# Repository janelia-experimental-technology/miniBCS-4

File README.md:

# miniBSC-4
 Configurable I/O PCB for Teensy 4.1 and Max11300
 
 https://doi.org/10.25378/janelia.29669162

 System Overview

The miniBCS is a compact, general-purpose Behavioral Control System (BCS). It provides a powerful platform to control real-time experiments. It is highly adaptable in terms of types of outputs and connectors. It is also designed to be easy to use, self-documenting, inexpensive, and easy to customize.

Hardware Development

The miniBCS is designed around the Teensy processor system. Currently, the Teensy 3.5 processor board is being used. This board utilizes a 32-bit ARM processor with 120Mhz operation, 512K Flash, and 192K RAM. The Arduino programming environment makes writing and downloading code easy. A MAX11300 integrated circuit provides 12-bit bipolar ADC/DAC and other configurable IO not available on the Teensy. The various input/outputs (IOs) are brought out to various connector options, including DB9, BNC, latch connectors, and RJ9. Connectors can face vertically or horizontally. A waveform generator is also built in. builders can add a small monochrome graphic LCD and three pushbuttons to provide a simple user interface. The system is designed so that only the required features and connectors need to be added to the base board, minimizing cost and assembly time. The enclosure can be made from laser-cut material, making it easy to configure the unit, house the electronics, make attachment points, and engrave connector labels.

Capabilities (some are mutually exclusive):

    Up to three RS232 serial ports
    Host USB serial port (also used for programming)
    CAN bus
    Ethernet
    Up to 10 12-bit DACs with +/-5V, 0-10V, or -10 to 10V ranges (MAX11300)
    Up to 10 12-bit ADCs with 0-2.5, +/-5V, 0-10V, or -10 to 0V ranges (MAX11300)
    Up to 10 IOs with programmable thresholds or output ranges (MAX11300)
    8 isolated solenoid drivers with 11-35 Volt power supply range
    Frequency Generator with a range of 1Hz to 10MHz, sine, triangle, square wave
    2 temperature sensors (MAX11300)
    SPI/I2C Expansion Bus
    Up to 8 IOs that connect directly to the processor that can be programmed for:
        Interrupts
        0-3.3V DAC
        0-3.3V ADC
        3.3V digital output
        5V tolerant digital input
        PWM or servo drive
        Various timer/counter needs

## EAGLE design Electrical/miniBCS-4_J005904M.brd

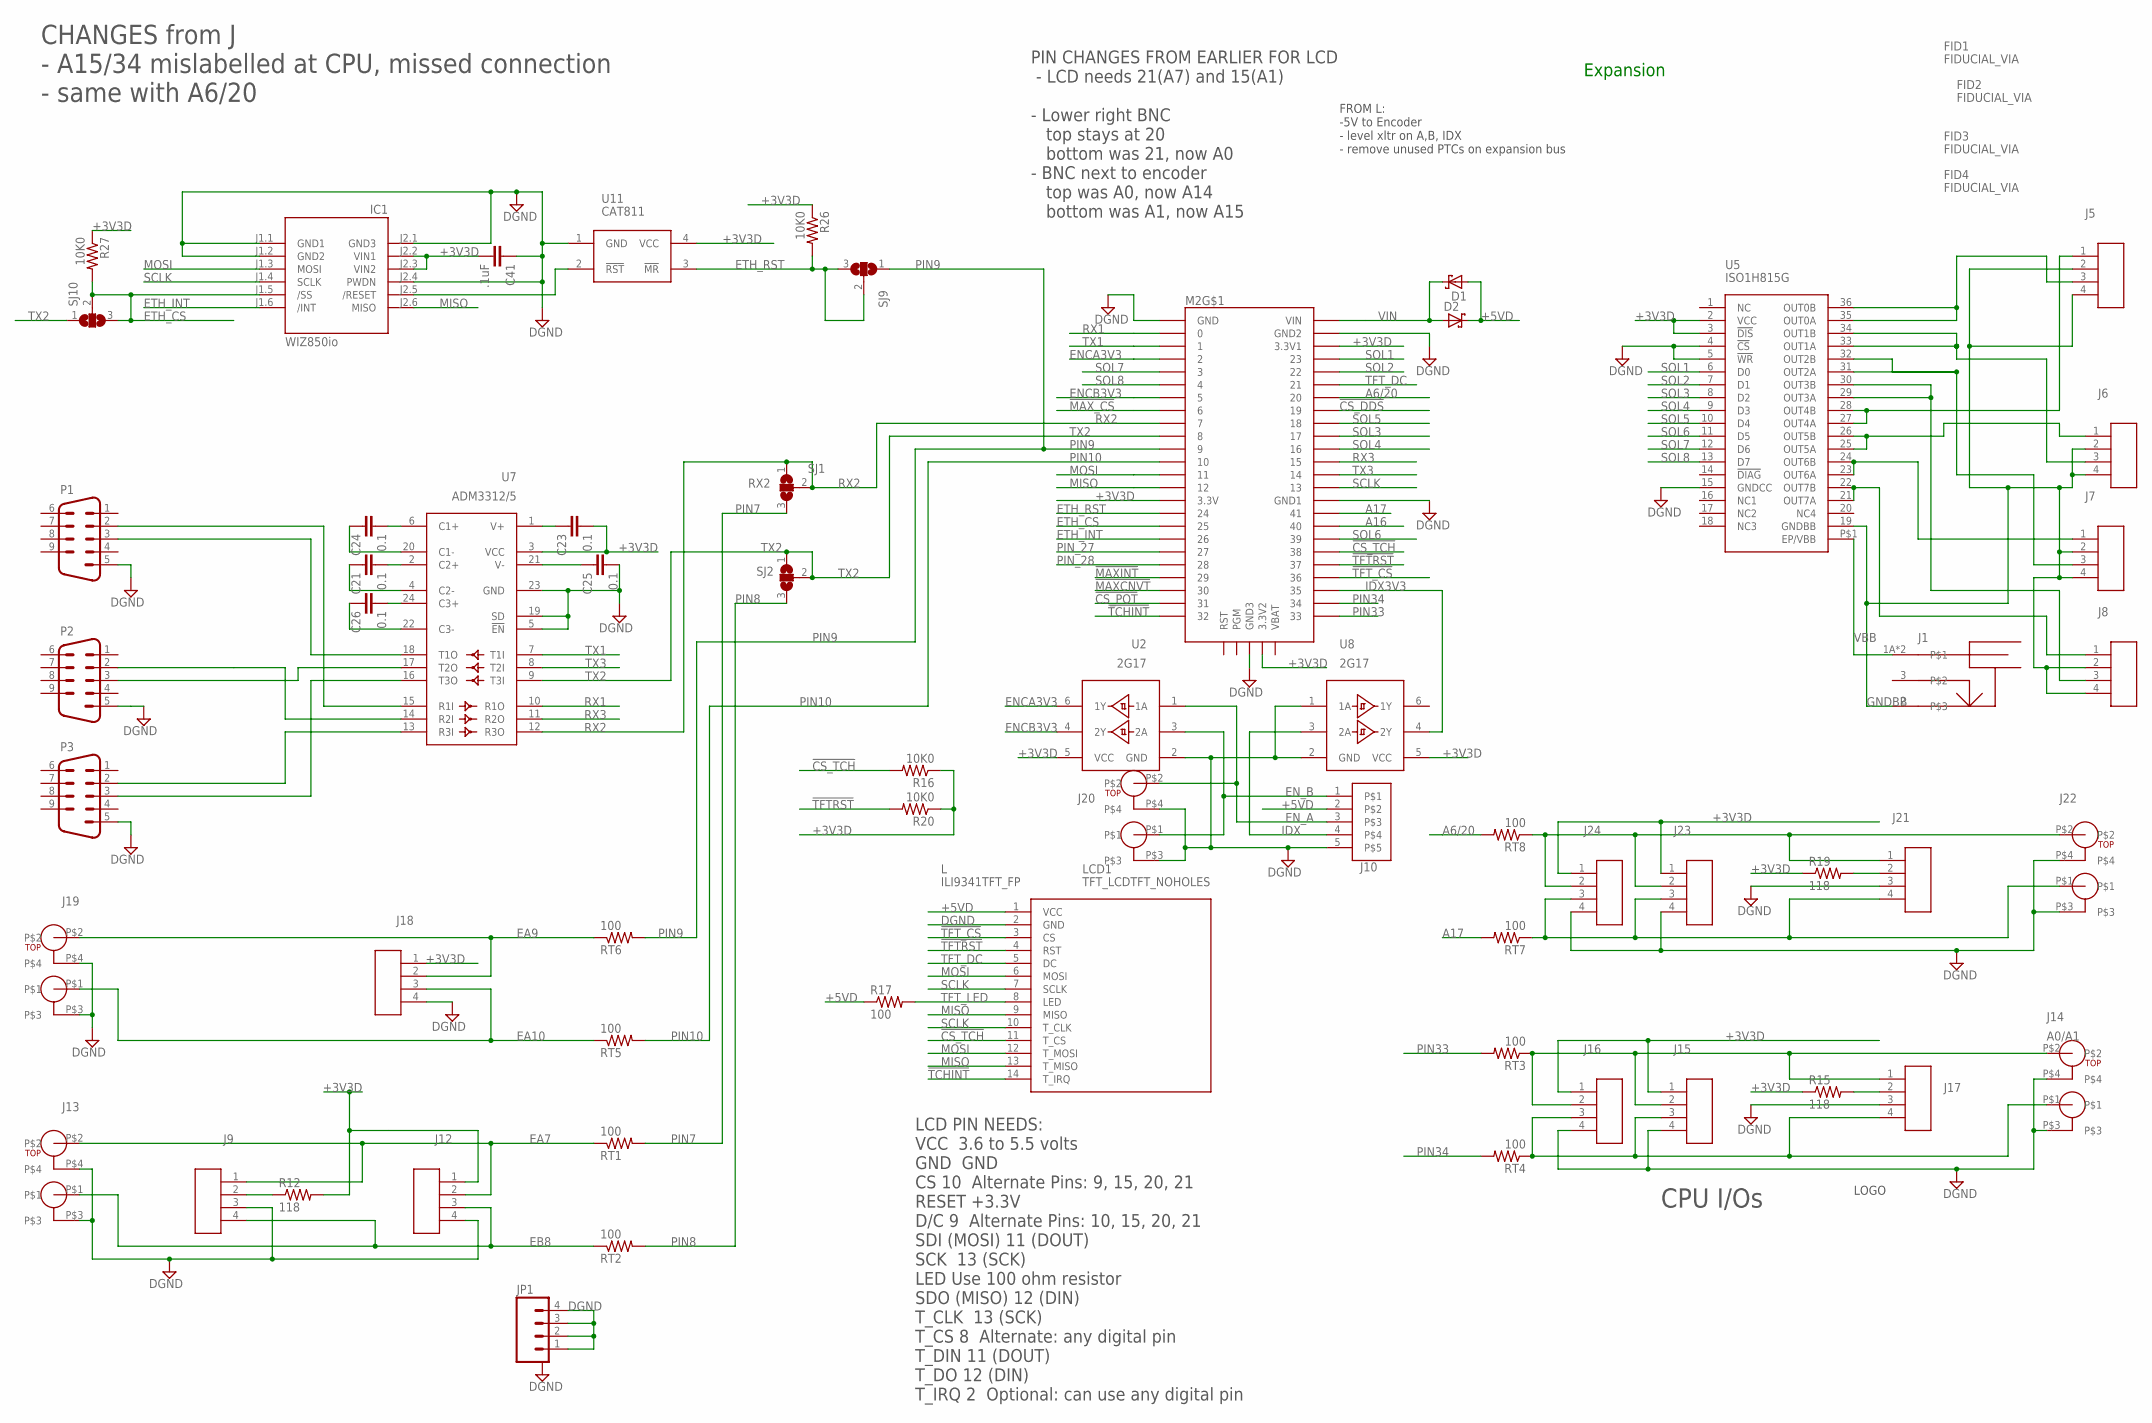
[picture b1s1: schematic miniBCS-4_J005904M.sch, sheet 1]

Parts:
C21, C23, C24, C25, C26: 0.1; 0603S
C41: .1uF; 0603S
D1, D2: SCHOTTKY-DIODESMD; SMB
FID1, FID2, FID3, FID4: FIDUCIAL_VIA
IC1: WIZ850io; WIZ820IO
J1: POWER_JACK_SHUNTPJ-002; PJ-002
J5, J6, J7, J8: CON41894804; 1894804
J9, J17, J21: RJ90432024101; 0432024101
J10: CON5AMPMODU-5; AMPMODU-5
J12, J15, J18, J23: CON4AMPMODUL-4-RA; AMPMODU-4-RA
J13, J19, J20, J22: BNC-DUAL; DUAL-BNC
J14: A0/A1; DUAL-BNC
J16, J24: CON41881464; PHOENIX_1881464
JP1: M04LOCK; 1X04_LOCK
L: ILI9341TFT_FP; ILI9341TFT_HOLES
LCD1: TFT_LCDTFT_NOHOLES; TFT_LCD_NOHOLES
M2: TEENSY4.1
P1, P2, P3: M09-182; 182-009-MALE
R12, R15, R19: 118; 0805S
R16, R20, R26, R27: 10K0; 0805S
R17: 100; 0805S
RT1, RT2, RT3, RT4, RT5, RT6, RT7, RT8: 100; 0805S
SJ1, SJ2, SJ9, SJ10: SJ2W; SJ_2
U2, U8: 2G17; SOT23-6
U5: ISO1H815G; PG-DSO-36
U7: ADM3312/5; TSSOP-24
U11: CAT811; SOT-143
U$1: JFRC-LOGOLOGO_2014_DOC; LOGO_JANELIA_2014_DOC

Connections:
!CS_DDS: M2.19/A5/SCL (19); also elsewhere on the board
!CS_POT: M2.31/A12 (31); also elsewhere on the board
!CS_TCH: LCD1.11 (T_CS), M2.38, R16.2
!MAXCNVT: M2.30; also elsewhere on the board
!MAXINT: M2.29; also elsewhere on the board
!MAX_CS: M2.6; also elsewhere on the board
!TCHINT: LCD1.14 (T_IRQ), M2.32
!TFTRST: LCD1.4 (RST), M2.37, R20.2
!TFT_CS: LCD1.3 (CS), M2.36
+3V3D: C23.2, C41.2, IC1.J2.2 (VIN1), IC1.J2.3 (VIN2), J12.1, J15.1, J16.1, J18.1, J23.1, J24.1, M2.3V3 (3.3V), M2.3V3_LO (3.3V1), M2.V33 (3.3V2), R12.2, R15.1, R16.1, R19.1, R20.1, R26.1, R27.1, U2.5 (VCC), U5.2 (VCC), U5.3 (!DIS), U7.3 (VCC), U8.5 (VCC), U11.4 (VCC); also elsewhere on the board
+5VD: D1.A, D2.C, J10.2, LCD1.1 (VCC), R17.1; also elsewhere on the board
A6/20: M2.20/A6 (20), RT8.2
A16: M2.40; also elsewhere on the board
A17: M2.41, RT7.2
DGND: C25.2, C41.1, IC1.J1.1 (GND1), IC1.J1.2 (GND2), IC1.J2.1 (GND3), IC1.J2.4 (PWDN), J9.3, J10.5, J12.4, J13.P$3, J13.P$4, J14.P$3, J14.P$4, J15.4, J16.4, J17.3, J18.4, J19.P$3, J19.P$4, J20.P$3, J20.P$4, J21.3, J22.P$3, J22.P$4, J23.4, J24.4, JP1.1, JP1.2, JP1.3, JP1.4, LCD1.2 (GND), M2.AGND (GND2), M2.GND, M2.GND1, M2.GND2 (GND3), P1.5, P2.5, P3.5, U2.2 (GND), U5.4 (!CS), U5.5 (!WR), U5.15 (GNDCC), U7.5 (!EN), U7.19 (SD), U7.23 (GND), U8.1 (1A), U8.2 (GND), U11.1 (GND); also elsewhere on the board
EA5: J14.P$2, J15.2, J16.2, J17.1, RT3.1
EA6: J21.1, J22.P$2, J23.2, J24.2, RT8.1
EA7: J9.1, J12.2, J13.P$2, RT1.1
EA9: J18.2, J19.P$2, RT6.1
EA10: J18.3, J19.P$1, RT5.1
EB5: J14.P$1, J15.3, J16.3, J17.4, RT4.1
EB6: J21.4, J22.P$1, J23.3, J24.3, RT7.1
EB8: J9.4, J12.3, J13.P$1, RT2.1
ENCA3V3: M2.2, U2.6 (1Y)
ENCB3V3: M2.5, U2.4 (2Y)
EN_A: J10.3, J20.P$2, U2.1 (1A)
EN_B: J10.1, J20.P$1, U2.3 (2A)
ETH_CS: IC1.J1.5 (/SS), M2.25, R27.2, SJ10.2, SJ10.3
ETH_INT: IC1.J1.6 (/INT), M2.26
ETH_RST: M2.24, R26.2, SJ9.2, SJ9.3, U11.3 (!MR)
GNDBB: J1.2, J5.2, J5.4, J6.2, J6.4, J7.2, J7.4, J8.2, J8.4, U5.19 (GNDBB)
IDX: J10.4, U8.3 (2A)
IDX3V3: M2.35, U8.4 (2Y)
MISO: IC1.J2.6 (MISO), LCD1.9 (MISO), LCD1.13 (T_MISO), M2.12/MISO (12); also elsewhere on the board
MOSI: IC1.J1.3 (MOSI), LCD1.6 (MOSI), LCD1.12 (T_MOSI), M2.11/MOSI (11); also elsewhere on the board
unnamed: J7.1, U5.23 (OUT6A), U5.24 (OUT6B)
unnamed: J9.2, R12.1
unnamed: J21.2, R19.2
unnamed: J17.2, R15.2
unnamed: P2.2, U7.14 (R2I)
unnamed: J5.1, U5.27 (OUT4A), U5.28 (OUT4B)
unnamed: P2.3, U7.17 (T2O)
unnamed: C23.1, U7.1 (V+)
unnamed: J6.1, U5.25 (OUT5A), U5.26 (OUT5B)
unnamed: C25.1, U7.21 (V-)
unnamed: P1.3, U7.18 (T1O)
unnamed: J8.3, U5.29 (OUT3A), U5.30 (OUT3B)
unnamed: J8.1, U5.21 (OUT7A), U5.22 (OUT7B)
unnamed: C26.2, U7.24 (C3+)
unnamed: C26.1, U7.22 (C3-)
unnamed: C21.1, U7.4 (C2-)
unnamed: C21.2, U7.2 (C2+)
unnamed: C24.1, U7.20 (C1-)
unnamed: P1.2, U7.15 (R1I)
unnamed: J5.3, U5.35 (OUT0A), U5.36 (OUT0B)
unnamed: C24.2, U7.6 (C1+)
unnamed: J6.3, U5.33 (OUT1A), U5.34 (OUT1B)
unnamed: J7.3, U5.31 (OUT2A), U5.32 (OUT2B)
unnamed: P3.3, U7.16 (T3O)
unnamed: IC1.J2.5 (/RESET), U11.2 (!RST)
PIN7: RT1.2, SJ1.3
PIN8: RT2.2, SJ2.3
PIN9: M2.9, RT6.2, SJ9.1
PIN10: M2.10/CS (10), RT5.2
PIN33: M2.33, RT3.2
PIN34: M2.34, RT4.2
PIN_27: M2.27; also elsewhere on the board
PIN_28: M2.28; also elsewhere on the board
RX1: M2.0/RX (0), U7.10 (R1O)
RX2: M2.7, SJ1.1, SJ1.2, U7.12 (R3O)
RX3: M2.15/A1 (15), U7.11 (R2O)
RX3_232: P3.2, U7.13 (R3I)
SCLK: IC1.J1.4 (SCLK), LCD1.7 (SCLK), LCD1.10 (T_CLK), M2.13/SCK (13); also elsewhere on the board
SOL1: M2.23/A9 (23), U5.6 (D0)
SOL2: M2.22/A8 (22), U5.7 (D1)
SOL3: M2.17/A3 (17), U5.8 (D2)
SOL4: M2.16/A2 (16), U5.9 (D3)
SOL5: M2.18/A4/SDA (18), U5.10 (D4)
SOL6: M2.39, U5.11 (D5)
SOL7: M2.3, U5.12 (D6)
SOL8: M2.4, U5.13 (D7)
TFT_DC: LCD1.5 (DC), M2.21/A7 (21)
TFT_LED: LCD1.8 (LED), R17.2
TX1: M2.1/TX (1), U7.7 (T1I)
TX2: M2.8, SJ2.1, SJ2.2, SJ10.1, U7.9 (T3I)
TX3: M2.14/A0 (14), U7.8 (T2I)
VBB: J1.1A, J1.1B, U5.P$1 (EP/VBB)
VIN: D1.C, D2.A, M2.VIN

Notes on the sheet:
CPU I/Os
Expansion
CHANGES from J - A15/34 mislabelled at CPU, missed connection - same with A6/20
PIN CHANGES FROM EARLIER FOR LCD - LCD needs 21(A7) and 15(A1) - Lower right BNC top stays at 20 bottom was 21, now A0 - BNC next to encoder top was A0, now A14 bottom was A1, now A15
LCD PIN NEEDS: VCC 3.6 to 5.5 volts GND GND CS 10 Alternate Pins: 9, 15, 20, 21 RESET +3.3V D/C 9 Alternate Pins: 10, 15, 20, 21 SDI (MOSI) 11 (DOUT) SCK 13 (SCK) LED Use 100 ohm resistor SDO (MISO) 12 (DIN) T_CLK 13 (SCK) T_CS 8 Alternate: any digital pin T_DIN 11 (DOUT) T_DO 12 (DIN) T_IRQ 2 Opti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
FROM L: -5V to Encoder - level xltr on A,B, IDX - remove unused PTCs on expansion bus

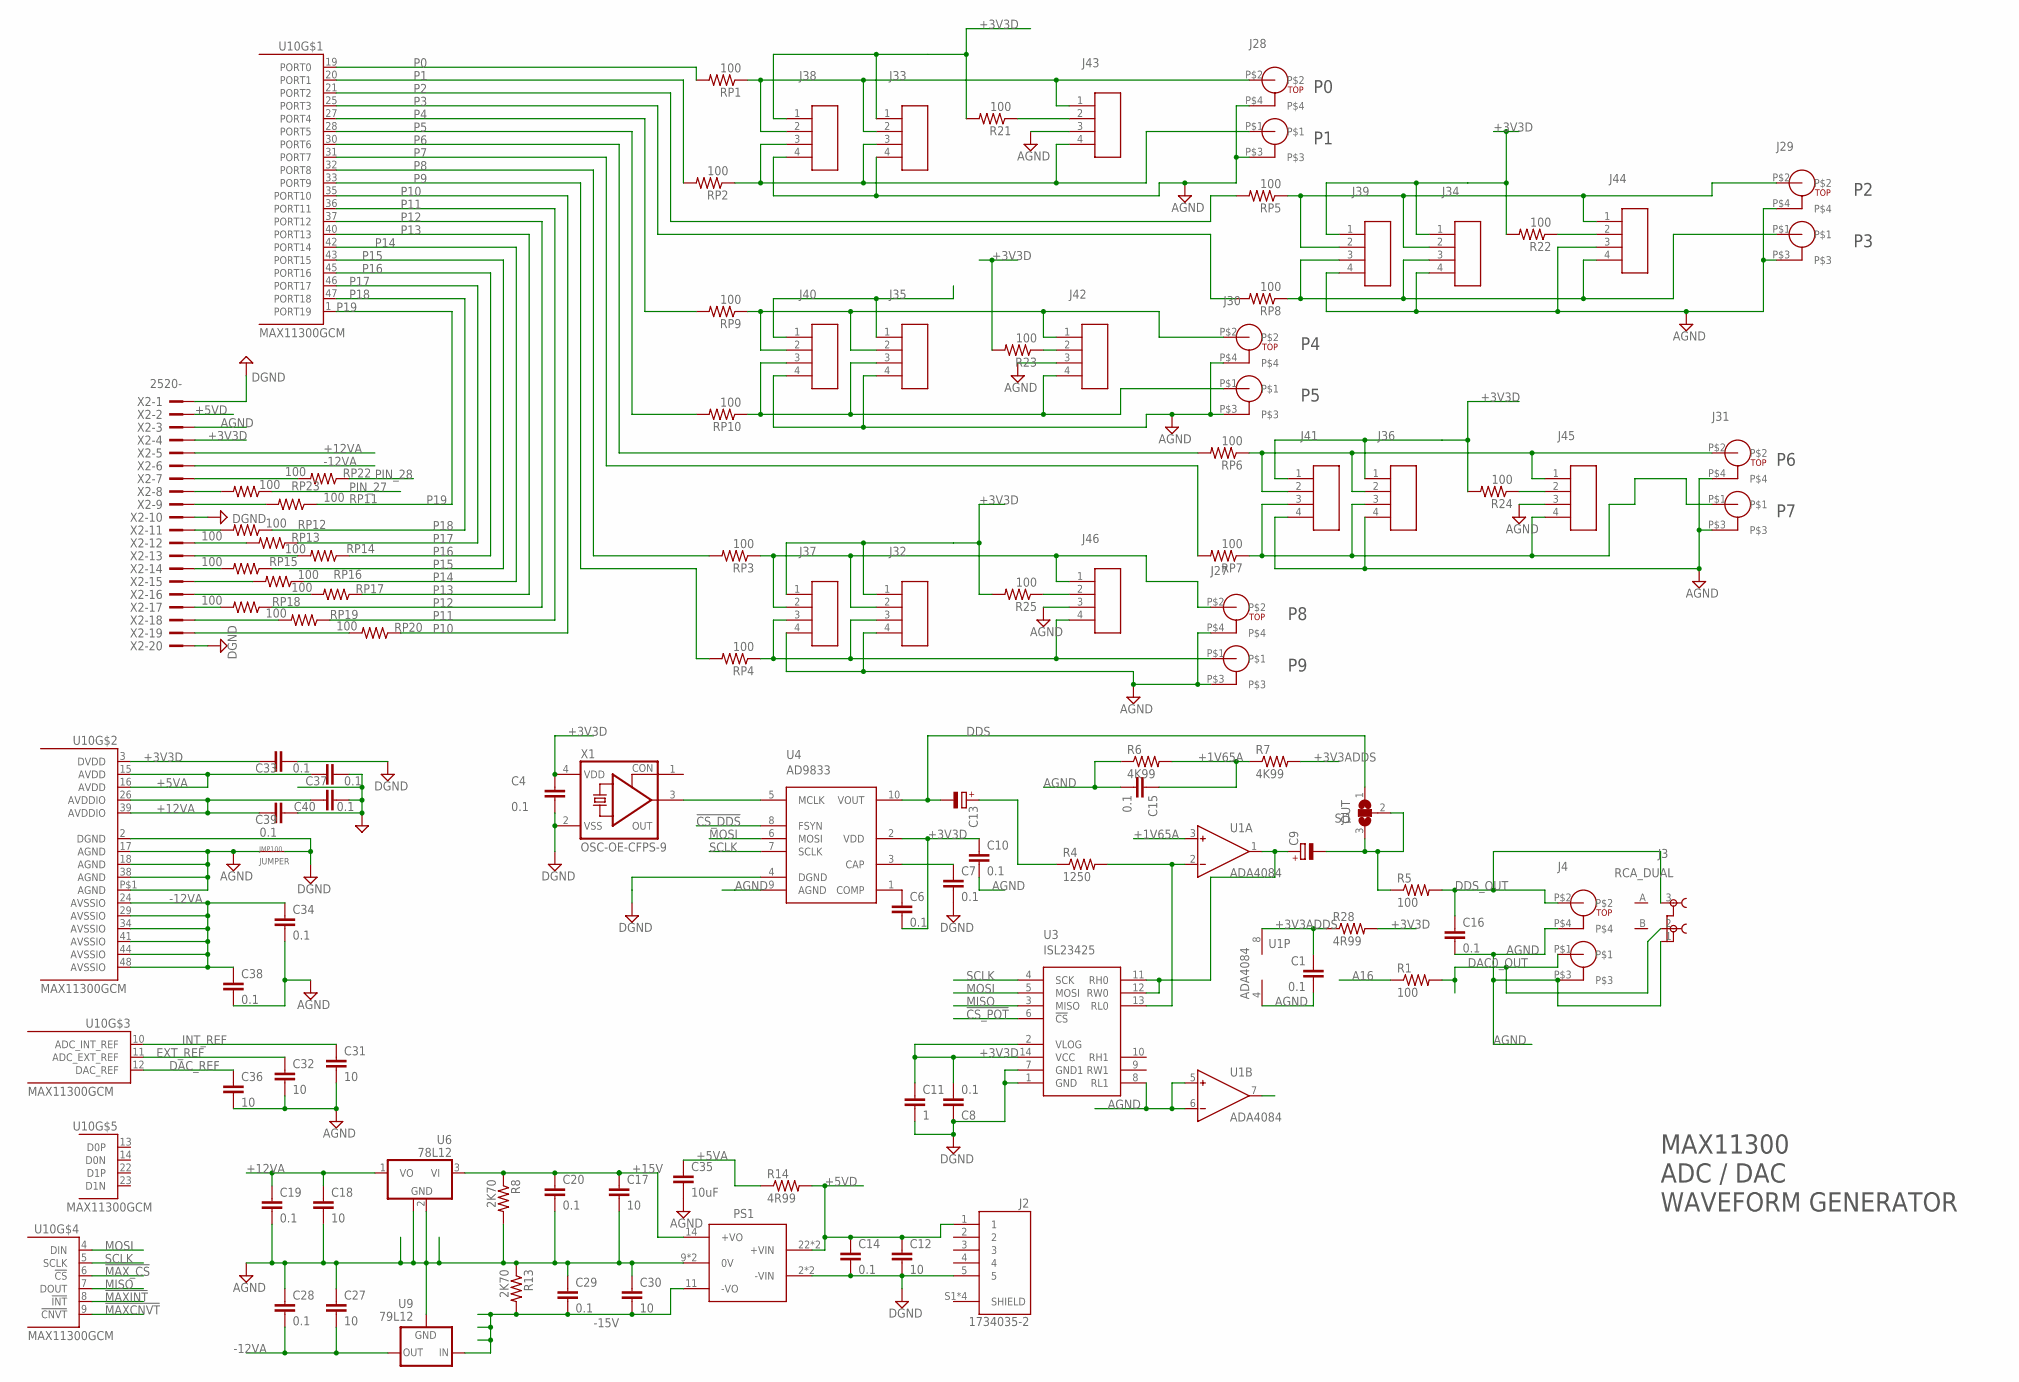
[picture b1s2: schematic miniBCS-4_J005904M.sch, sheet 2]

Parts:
C1, C4, C6, C7, C8, C10, C14, C15, C19, C20, C28, C29, C33, C34, C37, C38, C39, C40: 0.1; 0603S
C9, C13: CPOL-EUC; PANASONIC_C
C11: 1; 0805S
C12, C17, C18, C27, C30, C31, C32, C36: 10; 1206S
C16: 0.1; 0805S
C35: 10uF; 1206S
J2: 1734035-2; CONN_1734035-2
J3: RCA_DUAL; RCJ-22XX
J4, J27, J28, J29, J30, J31: BNC-DUAL; DUAL-BNC
J32, J33, J34, J35, J36: CON4AMPMODUL-4-RA; AMPMODU-4-RA
J37, J38, J39, J40, J41: CON41881464; PHOENIX_1881464
J42, J43, J44, J45, J46: RJ90432024101; 0432024101
JMP100: JUMPER
OUT: SJ1; SJ_2
PS1: DC-DC_NTANDTD; NDTD
R1, R5, R21, R22, R23, R24, R25: 100; 0805S
R4: 1250; 0805S
R6, R7: 4K99; 0805S
R8, R13: 2K70; 0805S
R14, R28: 4R99; 0805S
RP1, RP2, RP3, RP4, RP5, RP6, RP7, RP8, RP9, RP10, RP11, RP12, RP13, RP14, RP15, RP16, RP17, RP18, RP19, RP20, RP22, RP23: 100; 0805S
U1: ADA4084; SO8
U3: ISL23425; TSSOP14
U4: AD9833; MSOP10
U6: 78L12; SOT89
U9: 79L12; SOT89
U10: MAX11300GCM; TQFP48
X1: OSC-OE-CFPS-9; 5.2X3.4-4-PAD
X2: 2520-; PAK100/2500-20

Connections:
!CS_DDS: U4.8 (FSYN); also elsewhere on the board
!CS_POT: U3.6 (!CS); also elsewhere on the board
!MAXCNVT: U10.9 (!CNVT!); also elsewhere on the board
!MAXINT: U10.8 (!INT!); also elsewhere on the board
!MAX_CS: U10.6 (!CS!); also elsewhere on the board
+1V65A: C15.1, R6.2, R7.1, U1.3 (IN+)
+3V3ADDS: C1.1, R7.2, R28.1, U1.8 (V+)
+3V3D: C4.1, C6.2, C8.2, C10.1, C11.1, C33.1, J32.1, J33.1, J34.1, J36.1, J37.1, J38.1, J39.1, J41.1, R21.2, R22.2, R23.2, R24.2, R25.2, R28.2, U3.2 (VLOG), U3.14 (VCC), U4.2 (VDD), U10.3 (DVDD), X1.4 (VDD), X2.4; also elsewhere on the board
+5VA: C35.1, C37.1, R14.1, U10.15 (AVDD), U10.16 (AVDD)
+5VD: C12.1, C14.1, J2.1, PS1.22 (+VIN), PS1.23 (+VIN), R14.2, X2.2; also elsewhere on the board
+12VA: C18.1, C19.1, C39.1, C40.1, U6.1 (VO), U10.26 (AVDDIO), U10.39 (AVDDIO), X2.5
+15V: C17.1, C20.1, PS1.14 (+VO), R8.1, U6.3 (VI)
-12VA: C27.2, C28.2, C34.1, C38.1, U9.3 (OUT), U10.24 (AVSSIO), U10.29 (AVSSIO), U10.34 (AVSSIO), U10.41 (AVSSIO), U10.44 (AVSSIO), U10.48 (AVSSIO), X2.6
-15V: C29.2, C30.2, PS1.11 (-VO), R13.2, U9.2 (IN), U9.2@1 (IN)
A16: R1.1; also elsewhere on the board
AGND: C1.2, C10.2, C15.2, C16.2, C17.2, C18.2, C19.2, C20.2, C27.1, C28.1, C29.1, C30.1, C31.2, C32.2, C34.2, C35.2, C36.2, C37.2, C38.2, C39.2, C40.2, J3.1, J4.P$3, J4.P$4, J27.P$3, J27.P$4, J28.P$3, J28.P$4, J29.P$3, J29.P$4, J30.P$3, J30.P$4, J31.P$3, J31.P$4, J32.4, J33.4, J34.4, J35.4, J36.4, J37.4, J38.4, J39.4, J40.4, J41.4, J42.3, J43.3, J44.3, J45.3, J46.3, JMP100.1, PS1.9 (0V), PS1.16 (0V), R6.1, R8.2, R13.1, U1.4 (V-), U1.5 (IN+), U1.6 (IN-), U3.8 (RL1), U4.9 (AGND), U6.2 (GND), U6.2@1 (GND), U9.1 (GND), U10.17 (AGND), U10.18 (AGND), U10.38 (AGND), U10.P$1 (AGND), X2.3
DAC0_OUT: J3.2, J4.P$1, R1.2
DAC_REF: C36.1, U10.12 (DAC_REF)
DDS: C13.-, OUT.1, U4.10 (VOUT)
DDS_OUT: C16.1, J3.3, J4.P$2, R5.2
DGND: C4.2, C7.2, C8.1, C11.2, C12.2, C14.2, C33.2, J2.5, JMP100.2, PS1.2 (-VIN), PS1.3 (-VIN), U3.1 (GND), U3.7 (GND1), U4.4 (DGND), U10.2 (DGND), X1.2 (VSS), X2.1, X2.10, X2.20; also elsewhere on the board
EA: J28.P$2, J33.2, J38.2, J43.1, RP1.1
EA1: J29.P$2, J34.2, J39.2, J44.1, RP5.1
EA2: J30.P$2, J35.2, J40.2, J42.1, RP9.1
EA3: J31.P$2, J36.2, J41.2, J45.1, RP6.1
EA4: J27.P$2, J32.2, J37.2, J46.1, RP3.1
EB: J28.P$1, J33.3, J38.3, J43.4, RP2.1
EB1: J29.P$1, J34.3, J39.3, J44.4, RP8.1
EB2: J30.P$1, J35.3, J40.3, J42.4, RP10.1
EB3: J31.P$1, J36.3, J41.3, J45.4, RP7.1
EB4: J27.P$1, J32.3, J37.3, J46.4, RP4.1
EXT_REF: C32.1, U10.11 (ADC_EXT_REF)
INT_REF: C31.1, U10.10 (ADC_INT_REF)
MISO: U3.3 (MISO), U10.7 (DOUT); also elsewhere on the board
MOSI: U3.5 (MOSI), U4.6 (MOSI), U10.4 (DIN); also elsewhere on the board
unnamed: RP23.2, X2.8
unnamed: U4.5 (MCLK), X1.3 (OUT)
unnamed: C7.1, U4.3 (CAP)
unnamed: C6.1, U4.1 (COMP)
unnamed: J43.2, R21.1
unnamed: J42.2, R23.1
unnamed: J46.2, R25.1
unnamed: C13.+, R4.1
unnamed: J45.2, R24.1
unnamed: R4.2, U1.2 (IN-), U3.13 (RL0)
unnamed: C9.+, U1.1 (OUT), U3.11 (RH0), U3.12 (RW0)
unnamed: J44.2, R22.1
unnamed: RP15.2, X2.14
unnamed: RP14.2, X2.13
unnamed: RP20.2, X2.19
unnamed: RP19.2, X2.18
unnamed: RP18.2, X2.17
unnamed: RP17.2, X2.16
unnamed: RP16.2, X2.15
unnamed: RP13.2, X2.12
unnamed: RP12.2, X2.11
unnamed: RP11.2, X2.9
unnamed: RP22.2, X2.7
P0: RP1.2, U10.19 (PORT0)
P1: RP2.2, U10.20 (PORT1)
P2: RP5.2, U10.21 (PORT2)
P3: RP8.2, U10.25 (PORT3)
P4: RP9.2, U10.27 (PORT4)
P5: RP10.2, U10.28 (PORT5)
P6: RP6.2, U10.30 (PORT6)
P7: RP7.2, U10.31 (PORT7)
P8: RP3.2, U10.32 (PORT8)
P9: RP4.2, U10.33 (PORT9)
P10: RP20.1, U10.35 (PORT10)
P11: RP19.1, U10.36 (PORT11)
P12: RP18.1, U10.37 (PORT12)
P13: RP17.1, U10.40 (PORT13)
P14: RP16.1, U10.42 (PORT14)
P15: RP15.1, U10.43 (PORT15)
P16: RP14.1, U10.45 (PORT16)
P17: RP13.1, U10.46 (PORT17)
P18: RP12.1, U10.47 (PORT18)
P19: RP11.1, U10.1 (PORT19)
PIN_27: RP23.1; also elsewhere on the board
PIN_28: RP22.1; also elsewhere on the board
PWR_P4-5: J35.1, J40.1
SCLK: U3.4 (SCK), U4.7 (SCLK), U10.5 (SCLK); also elsewhere on the board
SJ1: C9.-, OUT.2, OUT.3, R5.1

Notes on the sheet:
MAX11300 ADC / DAC WAVEFORM GENERATOR

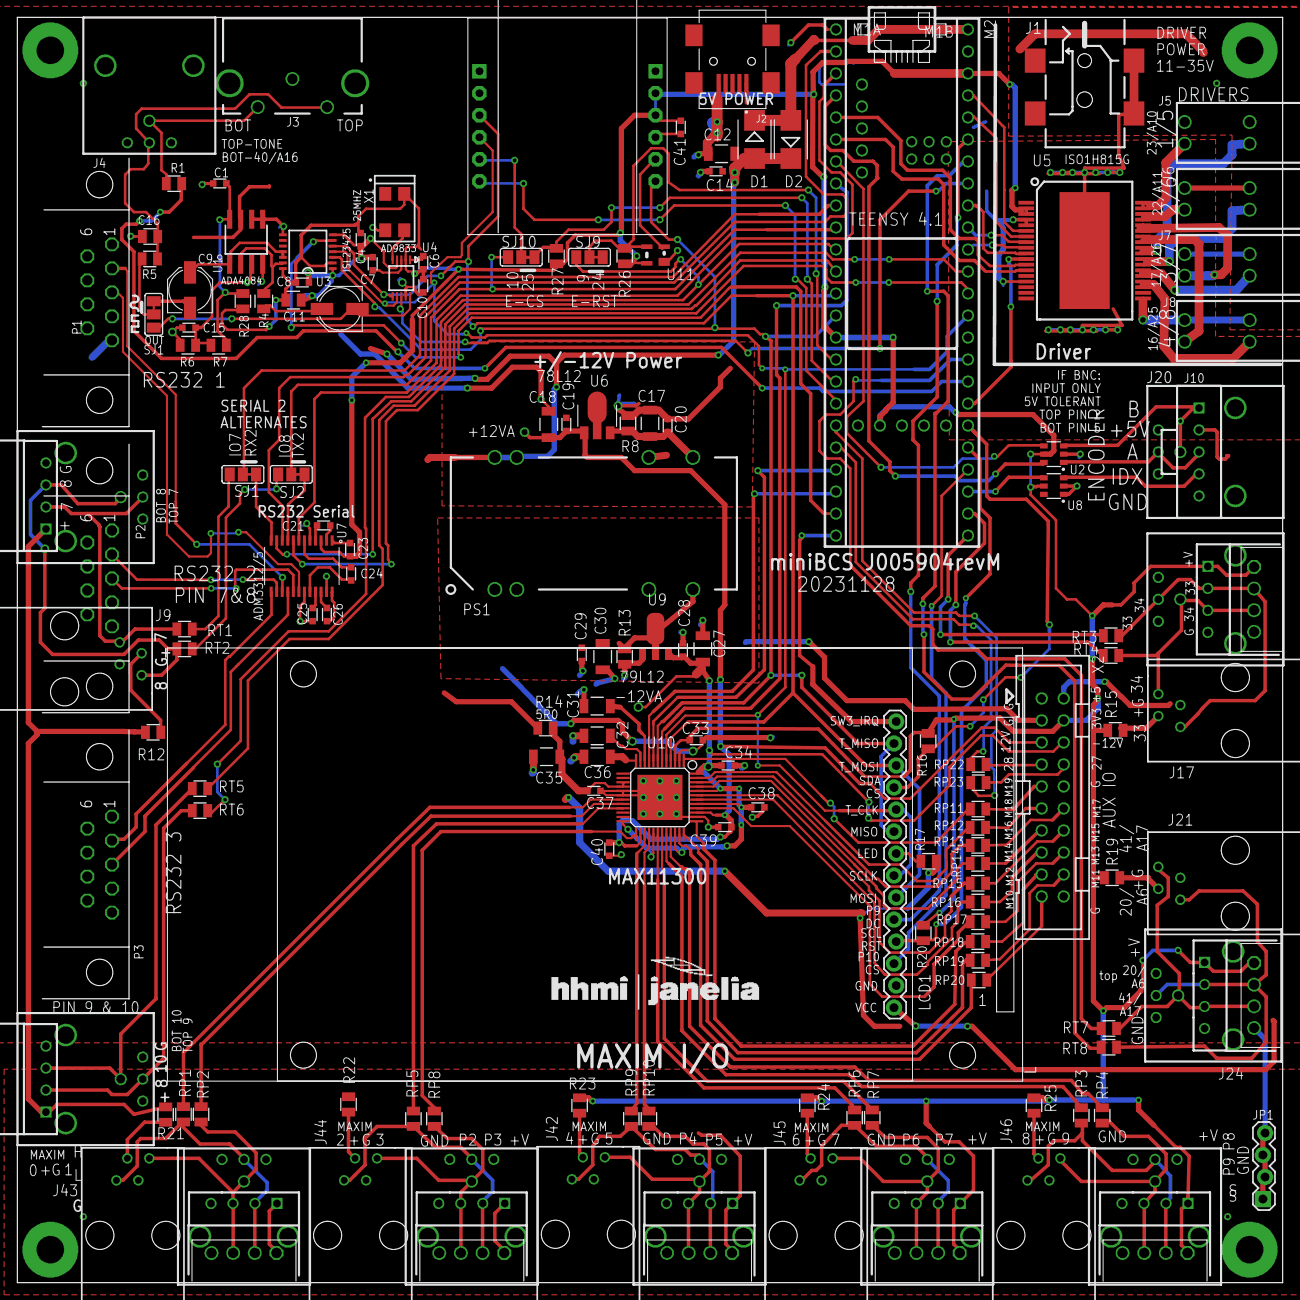
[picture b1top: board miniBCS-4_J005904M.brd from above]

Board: 2 copper layers, 146.1 x 146.1 mm, 167 parts (1 on the bottom side), 157 nets.

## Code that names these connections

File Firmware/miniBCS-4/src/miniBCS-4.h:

// ----------------------------------------------------------------------------
// miniBCS
// 
// functions needed for the miniBCS
//  set up solenoid pins, pushbutton pins 
//
// Author: Steve Sawtelle
// HHMI Janelia ID&F
// ----------------------------------------------------------------------------

// ---- VERSIONS  ----
#define  miniBCS_VERSION ((uint32_t) 20231129) 

// 0231129 sws
// - remove depracted Button code
// - changes for 'M' board with Teensy 4.1

// 20230518 sws
// - SOL7PIN was set to pin 4 and SOL8 to pin 3, but hardware is opposite, fix in FW

// 20221205 sws
// - solenoid pins 5-8 on Teesny 3.5 cannot be used as digital out
//   so set them the same as the T4.1. This will interfere with CAN 

// 20220822 sws
//  - add GPO pins 16 to 19 NOTE: Should also extend GPI and analog as well

// 20220613 sws 
// - alt pins for Teensy 4.1 - here and .cpp

// 20190322 sws
// - add CS setups for TFT and touchscreen so BCS can init properly

// 20190315 sws
// - mods for REV G boards
//  	- LCDCS now SPAREpin
//		- pin 15 now TFT CS
//		- SCL now TFT reset
//		- SDA now touchscreen CS
// 		- SW1 is TS int
// 		- 21 is TFT data/command

// 20170906 sws
// - add MAX code
// - workaround for problem with SPI settings
// 20170824 sws
// - change PB to use HW debounce
// - add encoder

// 20170817
// - started


#ifndef miniBCS_H
#define miniBCS_H

#include <SPI.h>

//volatile uint8_t _pushButtons = 0;

class miniBCS
{
 public:
 
//=======================================
// === P I N    D E F I N I T I O N S ===
// ======================================

#define RX1pin    0   // Serial 1 RX 
#define TX1pin    1   // Serial 1 TX
#define ENCApin   2   // encoder 'A' pin
#define SOL7pin   3 // Solenoid 7 pin
#define SOL8pin   4 // Solenoid 8 pin
#define ENCBpin   5   // encoder 'B' pin
#define MAXCSpin  6   // Chip Select for MAX112300
#ifdef ARDUINO_TEENSY41
#define RX2pin    7   // 
#else
#define RX3pin    7   // Serial 3 RX or 
#endif
#define PIN7      7   //   IO pin, with PWM
#ifdef ARDUINO_TEENSY41
#define TX2pin    8   // 
#else
#define TX3pin    8   // Serial 3 TX or
#endif
#define PIN8      8   //   IO pin with PWM
#define PIN9      9   //   IO pin with PWM
#ifndef ARDUINO_TEENSY41
#define RX2pin    9   // Serial 2 RX or
#define TX2pin    10  // Serial 3 TX or
#endif
#define PIN10     10  //   IO pin with PWM
#define ETHCSpin  10  // or alternate ethernet CS
#define MOSIpin   11  // SPI MOSI
#define MISOpin   12  // SPI MISO
#define SCLKpin   13  // SPI Clock
#ifdef ARDUINO_TEENSY41
#define TX3pin    14   // 
#endif
#define A0pin     14  // Analog in A0
#ifdef ARDUINO_TEENSY41
#define RX3pin    15
#else
#define TFTCSpin  15  // TFT chip select 
#endif
#define SOL4pin   16  // Solenoid 4 pin
#define SOL3pin   17  // Solenoid 3 pin
#define SOL5pin   18  // Solenoid 5 pin
#define DDSCSpin  19  // Chip Select for DDS
#define A6pin     20  // Analog in A6 
#define PIN20     20  //	or IO 20
#define TFTDCpin  21  // TFT Display command/data	or IO 21
#define SOL2pin   22  // Solenoid 2 pin
#define SOL1pin   23  // Solenoid 1 pin
#define ETH_RSTpin  24  // reserved for Ethernet
#define ETH_CS    25  // reserved for Ethernet
#define ETH26pin  26  // reserved for Ethernet
#define EXP8pin   27  // to Expansion Connection 8
#define EXP7pin   28  // to Expansion Connection 7
#define MAXINTpin 29  // interrupt in from MAX11300
#define MAXCVTpin 30  // ADC Convert signal to MAX11300
#define POTCSpin  31  // Chip Select for digital pot
#define TSINTpin  32  // touch screen interrupt	
#define PIN33     33  // I/O pin 33 w PWM
#define PIN34     34  // I/O pin 34 
#define IDXpin    35  // Encoder Index in
#ifdef ARDUINO_TEENSY41
#define TFTCSpin  36   // 
#else
#define LED1pin   36  // LED pin, Auxiliary I/O, analog, PWM for auxiliary connector - depracted 'M' rev and later 
#endif
#define TFTRSTpin 37  // TFT RESET  analog, PWM , SCL
#define TSCSpin   38  // Touchscreen CS, SDA
#define SOL6pin   39 // Solenoid 6 pin
#ifndef ARDUINO_TEENSY41
#define DAC0pin   A21 // DAC0 out pin (must be jumpered)
#define DAC1pin   A22 // DAC1 out pin (must be jumpered)
#endif


// DDS output waveform types
#define TONE_SINE     0x0000
#define TONE_TRIANGLE 0x0002  
#define TONE_SQUARE   0x0028   
#define TONE_DIVIDE   0x0020  


// MAX11300 defines
#define DAC_DATA_PORT_00 0x60
#define GPO_DATA_15_TO_0 0x0d
#define GPO_DATA_19_TO_16 0x0e
#define ADC_DATA_PORT_00 0x40
#define GPI_DATA_15_TO_0 0x0b
#define INT_TEMP		 0x08
#define EXT_TEMP1		 0x09
#define EXT_TEMP2		 0x0a
#define MAX_INT				0x01
#define MAX_ADCFLAG_MASK	0x0001
#define MAX_ADCST_L			0x02	
#define MAX_ADCST_H			0x03
#define MAX_ADCDM_MASK		0x0004
#define MAX_ADCDR_MASK		0x0002	
#define MAX_ADCFLAG_MASK	0x0001


  miniBCS(void);
  
  void begin();
  void driverOn(uint8_t ch);					// turn on driver channel 'ch'
  void driverOff(uint8_t ch);					// turn off driver channel 'ch'
  int8_t getDriver(uint8_t ch);					// get status of channel 'ch' (false = off)
  uint32_t getVersion(void);					// get library version (year,month,date )
  void setToneGain(uint8_t level);				// set tone output level (0-255)
  void toneReset(void);							// reset tone generator chip
  int8_t setTone( float freq, uint16_t mode);	// set tone frequency and waveform type	
  void toneOn(void);							// enable tone (that has already been set up)
  void toneOff(void);							// disable tone without changing parameters	
  int32_t getPosition(void);					// get encoder position (cumulative counts)
  void  setPosition(int32_t newpos);			// set encoder position to a value
  uint16_t getToneMode(void); 					// read waveform type set on tone generator
 
   
 private:
 
  const static uint16_t DDS_CONTROL =  0x2000;   // 0010 0000 0000 0000
  const static uint32_t DDS_MCLK = 25000000;  
  const static uint32_t DDS_2_28 = 268435456; 
 
  // Private Constants
  volatile uint32_t encoderCount;
  volatile float distancePerTick;
  volatile float speedPerTickPerSec;
  volatile uint32_t zeroMillis;
  
  uint16_t freqMode; 
  uint32_t ifreq;
  uint16_t fwordl;
  uint16_t  fwordh;
  uint8_t SOUND_ON_OFF = 1; //each channel is off to begin with, correlating to a value of 1 for D6
  const uint8_t driverPin[9] = {0, SOL1pin, SOL2pin, SOL3pin, SOL4pin, SOL5pin, SOL6pin, SOL7pin, SOL8pin};
  int8_t driverOnOff = 0x00;

};  // endclass miniBCS


#endif // miniBCS

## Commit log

2024-05-08 Board Update 20240508
    Add qwiic and SPI external connections
2024-05-21 Add SPI and I2C connectors
    Add external connections for SPI with two chip selects on 10 pin ribbon or 7 pin header
    Add QWIIC I2C connection
2024-07-17 Updated BOM, PCB files, example, and laser cut file
    Add QWIIC and SPI connector cutouts to laser file
2025-01-11 Update BOM. example code
2025-06-18 FW Update
2025-07-28 Update example and PCB
2026-06-15 add DOI

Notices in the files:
parts and their libraries:
SparkFun: Licensing: CC v3.0 Share-Alike You are welcome to use this library for commercial purposes.
